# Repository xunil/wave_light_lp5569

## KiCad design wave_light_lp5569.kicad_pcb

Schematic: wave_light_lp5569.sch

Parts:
C1, C2, C3, C4, C5, C6: 1uF; C_0805_HandSoldering
H1, H2, H3: MountingHole; MountingHole_2.7mm_Pad
J1, J3: Conn_01x06_Male; JST_PH_B6B-PH-K_1x06_P2.00mm_Vertical
J2, J5: Conn_01x09_Male; JST_PH_B9B-PH-K_1x09_P2.00mm_Vertical
J14: Conn_01x02_Male; JST_XH_B2B-XH-A_1x02_P2.50mm_Vertical
JP1, JP2, JP3, JP4: SolderJumper_2_Open; SolderJumper-2_P1.3mm_Open_RoundedPad1.0x1.5mm
JP5: SolderJumper_3_Bridged12; SolderJumper-3_P1.3mm_Bridged12_RoundedPad1.0x1.5mm
R1: 120k; R_0805_HandSoldering
R2, R3: 2.2k; R_0805_HandSoldering
U1: LP3990; SOT-23-5_HandSoldering
U2: LP5569; WQFN-24-1EP_4x4mm_P0.5mm_EP2.6x2.6mm

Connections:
ADDR: JP1.2 (B), JP2.2 (B), JP3.2 (B), JP4.2 (B), U2.20 (ADDR)
CLK: J1.4, J3.4, U2.6 (CLK)
EN_PWM: J1.3, J3.3, U2.5 (EN/PWM)
GND: C1.1, C2.1, C3.1, C6.1, J1.6, J3.6, J14.1, JP1.1 (A), U1.2 (GND), U2.4 (AGND), U2.21 (PGND)
GPIO_TRIG_INT: J1.5, J3.5, R1.2, U2.7 (GPIO/TRIG/INT)
LED0: J5.1, U2.19 (LED0)
LED1: J5.2, U2.18 (LED1)
LED2: J5.3, U2.17 (LED2)
LED3: J5.4, U2.16 (LED3)
LED4: J5.5, U2.15 (LED4)
LED5: J5.6, U2.14 (LED5)
LED6: J5.7, U2.13 (LED6)
LED7: J5.8, U2.12 (LED7)
LED8: J5.9, U2.11 (LED8)
unnamed: C4.1, U2.2 (C1+)
unnamed: C4.2, U2.24 (C1-)
unnamed: C5.1, U2.1 (C2+)
unnamed: C5.2, U2.23 (C2-)
SCL: J1.1, J3.1, JP2.1 (A), R2.2, U2.9 (SCL)
SDA: J1.2, J3.2, JP3.1 (A), R3.2, U2.8 (SDA)
V1P8: C2.2, U1.5 (OUT), U2.10 (V1P8)
VIN: C1.2, C3.2, J14.2, JP4.1 (A), JP5.1 (A), R1.1, R2.1, R3.1, U1.1 (IN), U1.3 (EN), U2.3 (VIN)
VLED: J2.1, J2.2, J2.3, J2.4, J2.5, J2.6, J2.7, J2.8, J2.9, JP5.2 (C)
VOUT: C6.2, JP5.3 (B), U2.22 (VOUT)

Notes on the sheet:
1.8V LDO Regulator
Address Selection
Logic Inputs
LED Power Rail Selection
LED Connections
Logic Outputs
I2C Pullups
GPIO Pullup
Only populate on first board
32h and 40h
33h and 40h
34h and 40h
35h and 40h
Add 10h to individual address for LP5569A
LED Controller
Use Charge Pump Output
Use Input Voltage
Common Pin
TODO: Figure out external clock; internal clock doesn't want to come out the clock pin

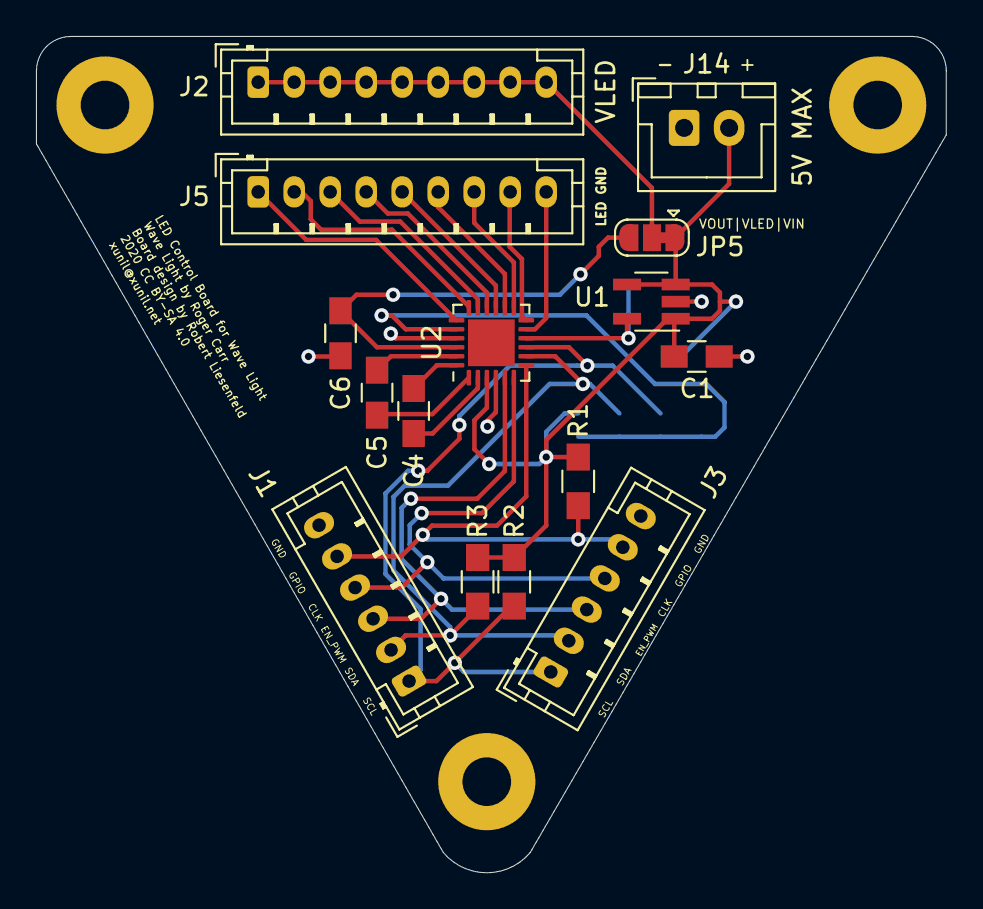
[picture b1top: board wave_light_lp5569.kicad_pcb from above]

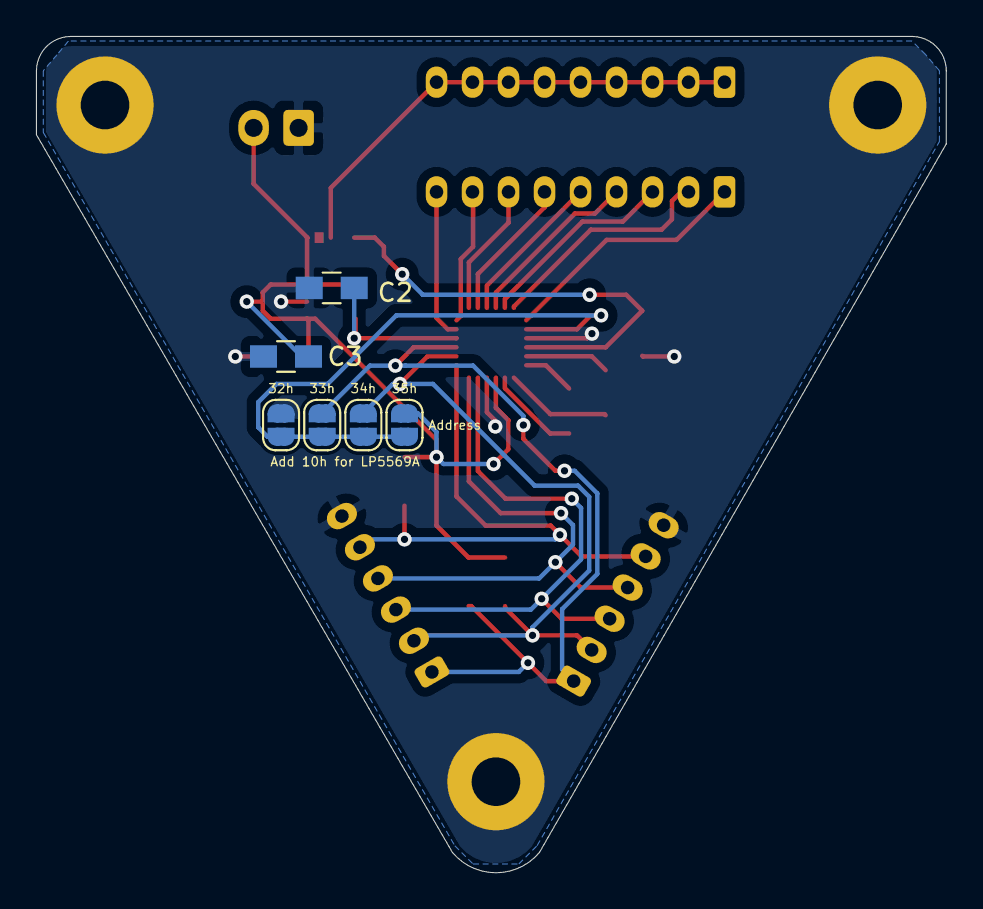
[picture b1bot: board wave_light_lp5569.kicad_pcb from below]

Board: 2 copper layers, 50.5 x 46.5 mm, 24 parts (6 on the bottom side), 24 nets.

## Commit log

2020-06-23 New LED control board for the wave light based around the LP5569
2020-08-05 Initial checkin of Python code for testing LP5569 board
2020-08-17 Added a bunch of debugging code to the Python library.
2020-08-17 Freezing Python library requirements
2020-08-17 Schematic PDF
2020-12-05 First go at a wedge-shaped board
2020-12-05 Attempting to have clock signal output on clock pin
2020-12-05 Committing changes from last edit session, months ago
2020-12-05 Attempting to get the clock pin to output internal clock
2020-12-07 Still trying to get internal clock output working
2020-12-16 Checkpointing work on the wedge board
2020-12-24 Skeleton of Forth cross-assembler for LP5569 execution engines
2020-12-26 Finally passing ERC and DRC, seems ready to send off for fab
2020-12-26 Adding board render
2020-12-26 Zero-arg instructions working, 1-arg immediate instructions are or'ing the wrong byte
2020-12-28 Minor edits, still have a bug in instr_or
2020-12-28 Ramp still not working
2020-12-29 rot not swap - ramp now works
2020-12-31 Added branch instruction - not yet tested
2021-01-02 Added conditional branch instructions, still untested
2021-01-07 Use step word instead of recalculating from pc every time
2021-01-07 Final version, sent to fab
2021-01-08 Working on a fixup table implementation, need to figure out how to signal success or failure on lookup
2021-03-30 Added begin/end broadcast functions, messing with controlling multiple nodes
2021-04-23 Added some abstraction about the object's I2C address to allow for multiple wave light boards

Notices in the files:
wave_light_lp5569.kicad_pcb:
2020 CC BY-SA 4.0
